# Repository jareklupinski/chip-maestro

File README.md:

# chip-maestro
An NES Cartridge with a MIDI Input Jack

After watching Anamanaguchi play a live show with a NES MIDI Tracker, I wanted to create a live instrument they could play on-stage.

It's been a while since I worked on this. I'm sorry about the CPLD part, it was a good idea then but now it would desperately need an update, probably to one of those microcontrollers with built-in configurable logic blocks.

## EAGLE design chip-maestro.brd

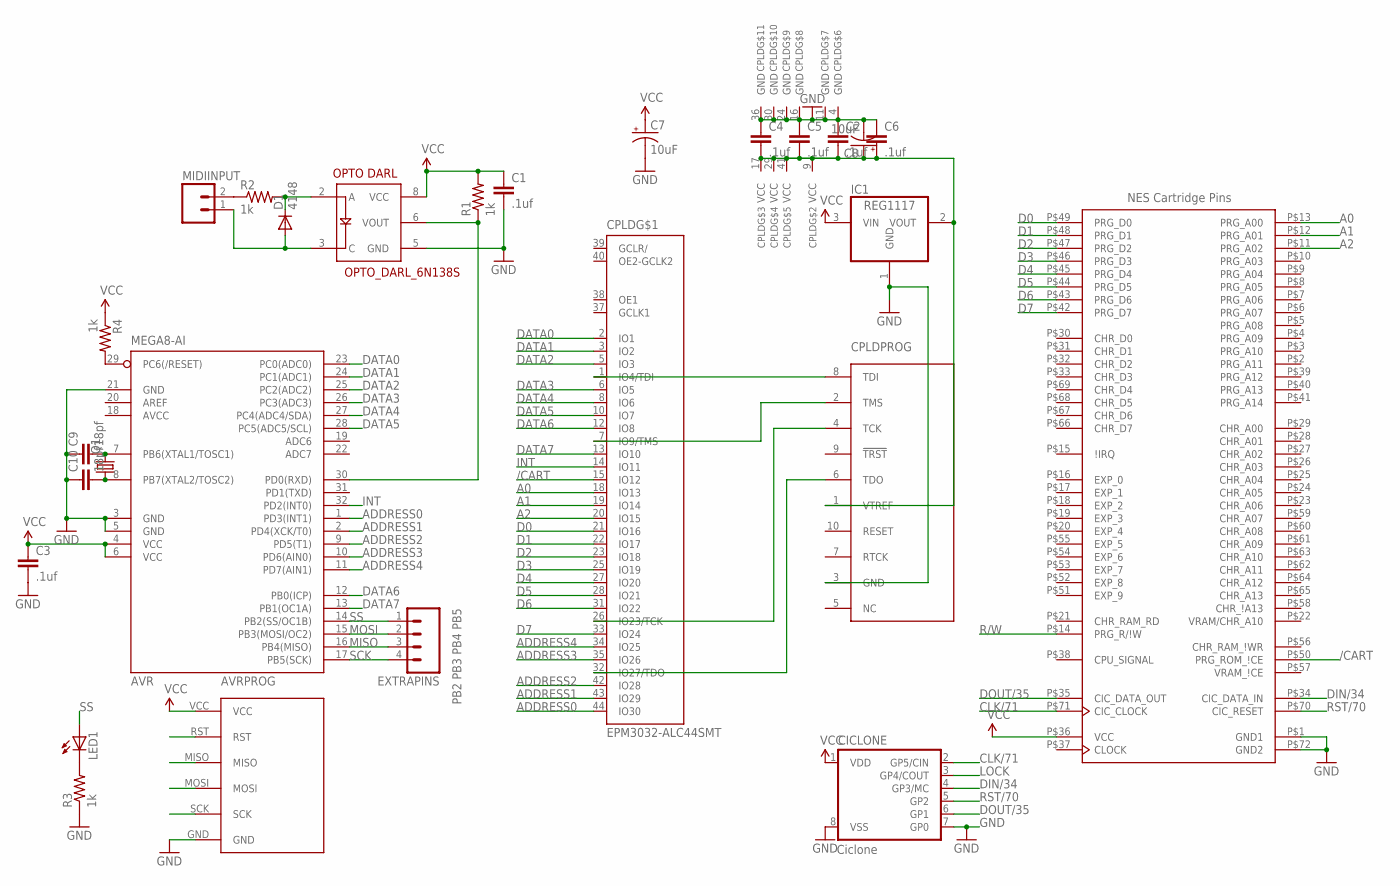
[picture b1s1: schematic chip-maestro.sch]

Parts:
AVR: MEGA8-AI; TQFP32-08
AVRPROG: 6PIN
C1, C2, C3, C4, C5, C6: .1uf; C0805K
C7, C8: 10uF; EIA3216
C9, C10: 18pf; C0805K
CICLONE: Ciclone; DIL8
CPLD: EPM3032-ALC44SMT; TQFP44
CPLDPROG: TC2050-MCP-NL; TC2030-MCP-NL
D1: 4148; SOT23-3
EXTRAPINS: PB2 PB3 PB4 PB5; 1X04
IC1: REG1117; SOT223
LED1: LEDCHIP-LED0805; CHIP-LED0805
MIDIINPUT: M02JST-PTH-2; JST-2-PTH
NESCARTPINS: NES-EDGE'; NES-EDGE
OPTO: OPTO_DARL_6N138S; 8-SMD
Q1: CRYSTALHC49UP; HC49UP
R1, R2, R3, R4: 1k; M0805

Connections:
/CART: CPLD.15 (IO12), NESCARTPINS.P$50 (PRG_ROM_\!CE)
A0: CPLD.18 (IO13), NESCARTPINS.P$13 (PRG_A00)
A1: CPLD.19 (IO14), NESCARTPINS.P$12 (PRG_A01)
A2: CPLD.20 (IO15), NESCARTPINS.P$11 (PRG_A02)
ADDRESS0: AVR.1 (PD3(INT1)), CPLD.44 (IO30)
ADDRESS1: AVR.2 (PD4(XCK/T0)), CPLD.43 (IO29)
ADDRESS2: AVR.9 (PD5(T1)), CPLD.42 (IO28)
ADDRESS3: AVR.10 (PD6(AIN0)), CPLD.35 (IO26)
ADDRESS4: AVR.11 (PD7(AIN1)), CPLD.34 (IO25)
AVCC: AVR.18 (AVCC)
CLK/71: CICLONE.2 (GP5/CIN), NESCARTPINS.P$71 (CIC_CLOCK)
D0: CPLD.21 (IO16), NESCARTPINS.P$49 (PRG_D0)
D1: CPLD.22 (IO17), NESCARTPINS.P$48 (PRG_D1)
D2: CPLD.23 (IO18), NESCARTPINS.P$47 (PRG_D2)
D3: CPLD.25 (IO19), NESCARTPINS.P$46 (PRG_D3)
D4: CPLD.27 (IO20), NESCARTPINS.P$45 (PRG_D4)
D5: CPLD.28 (IO21), NESCARTPINS.P$44 (PRG_D5)
D6: CPLD.31 (IO22), NESCARTPINS.P$43 (PRG_D6)
D7: CPLD.33 (IO24), NESCARTPINS.P$42 (PRG_D7)
DATA0: AVR.23 (PC0(ADC0)), CPLD.2 (IO1)
DATA1: AVR.24 (PC1(ADC1)), CPLD.3 (IO2)
DATA2: AVR.25 (PC2(ADC2)), CPLD.5 (IO3)
DATA3: AVR.26 (PC3(ADC3)), CPLD.6 (IO5)
DATA4: AVR.27 (PC4(ADC4/SDA)), CPLD.8 (IO6)
DATA5: AVR.28 (PC5(ADC5/SCL)), CPLD.10 (IO7)
DATA6: AVR.12 (PB0(ICP)), CPLD.12 (IO8)
DATA7: AVR.13 (PB1(OC1A)), CPLD.13 (IO10)
DIN/34: CICLONE.4 (GP3/MC), NESCARTPINS.P$34 (CIC_DATA_IN)
DOUT/35: CICLONE.6 (GP1), NESCARTPINS.P$35 (CIC_DATA_OUT)
GND: AVR.3 (GND), AVR.5 (GND), AVR.21 (GND), AVRPROG.GND, C1.2, C2.1, C3.2, C4.1, C5.1, C6.1, C7.C (-), C8.C (-), C9.1, C10.1, CICLONE.7 (GP0), CICLONE.8 (VSS), CPLD.4 (GND), CPLD.11 (GND), CPLD.16 (GND), CPLD.24 (GND), CPLD.30 (GND), CPLD.36 (GND), CPLDPROG.3 (GND), IC1.1 (GND), NESCARTPINS.P$1 (GND1), NESCARTPINS.P$72 (GND2), OPTO.5 (GND), R3.1
INT: AVR.32 (PD2(INT0)), CPLD.14 (IO11)
LOCK: CICLONE.3 (GP4/COUT)
MISO: AVR.16 (PB4(MISO)), AVRPROG.MISO, EXTRAPINS.3
MOSI: AVR.15 (PB3(MOSI/OC2)), AVRPROG.MOSI, EXTRAPINS.2
unnamed: LED1.C, R3.2
unnamed: AVR.8 (PB7(XTAL2/TOSC2)), C10.2, Q1.1
unnamed: CPLD.26 (IO23/TCK), CPLDPROG.4 (TCK)
unnamed: CPLD.32 (IO27/TDO), CPLDPROG.6 (TDO)
unnamed: CPLD.1 (IO4/TDI), CPLDPROG.8 (TDI)
unnamed: MIDIINPUT.2, R2.1
unnamed: AVR.7 (PB6(XTAL1/TOSC1)), C9.2, Q1.2
unnamed: CPLD.7 (IO9/TMS), CPLDPROG.2 (TMS)
unnamed: AVR.30 (PD0(RXD)), OPTO.6 (VOUT), R1.1
unnamed: D1.3 (C), OPTO.2 (A), R2.2
unnamed: D1.1 (A), MIDIINPUT.1, OPTO.3 (C)
R/W: NESCARTPINS.P$14 (PRG_R/\!W)
RST: AVR.29 (PC6(/RESET)), AVRPROG.RST, R4.2
RST/70: CICLONE.5 (GP2), NESCARTPINS.P$70 (CIC_RESET)
SCK: AVR.17 (PB5(SCK)), AVRPROG.SCK, EXTRAPINS.4
SS: AVR.14 (PB2(SS/OC1B)), EXTRAPINS.1, LED1.A
VCC: AVR.4 (VCC), AVR.6 (VCC), AVRPROG.VCC, C1.1, C3.1, C7.A (+), CICLONE.1 (VDD), IC1.3 (VIN), NESCARTPINS.P$36 (VCC), OPTO.8 (VCC), R1.2, R4.1
VCC2: C2.2, C4.2, C5.2, C6.2, C8.A (+), CPLD.9 (VCC), CPLD.17 (VCC), CPLD.29 (VCC), CPLD.41 (VCC), CPLDPROG.1 (VTREF), IC1.2 (VOUT)

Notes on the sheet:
NES Cartridge Pins

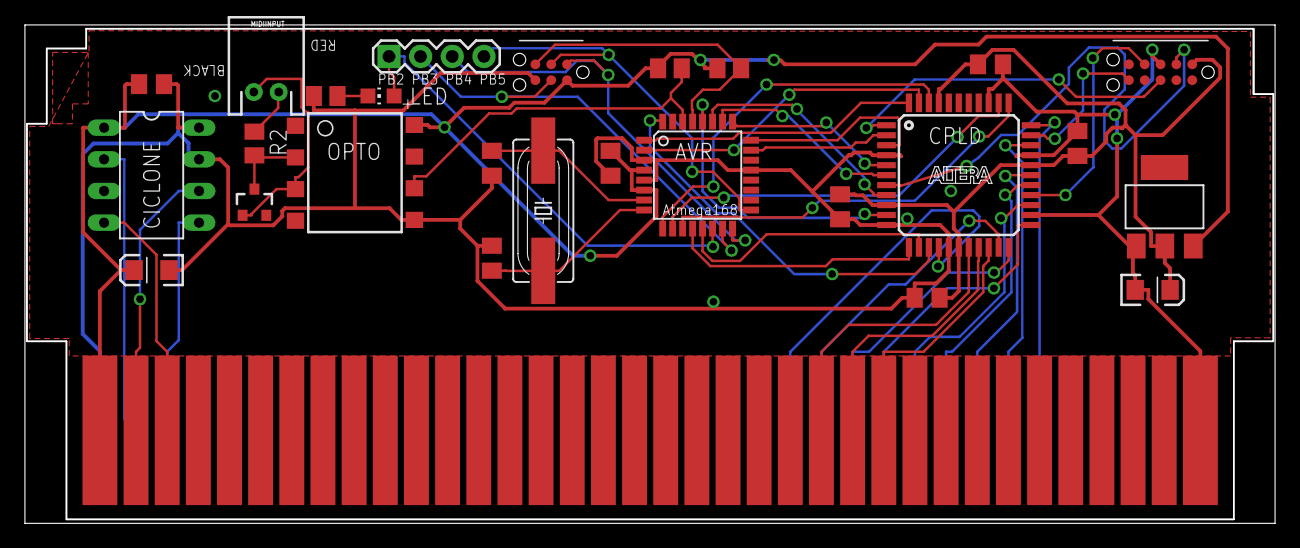
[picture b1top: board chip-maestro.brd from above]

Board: 2 copper layers, 100.2 x 39.9 mm, 27 parts (0 on the bottom side), 49 nets.

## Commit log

2018-07-04 design tested: working
2018-07-04 added pictures

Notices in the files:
parts and their libraries:
SparkFun-Capacitors: Licensing: CC v3.0 Share-Alike You are welcome to use this library for commercial purposes.
TC2050: ©2009 ROFA.cz
